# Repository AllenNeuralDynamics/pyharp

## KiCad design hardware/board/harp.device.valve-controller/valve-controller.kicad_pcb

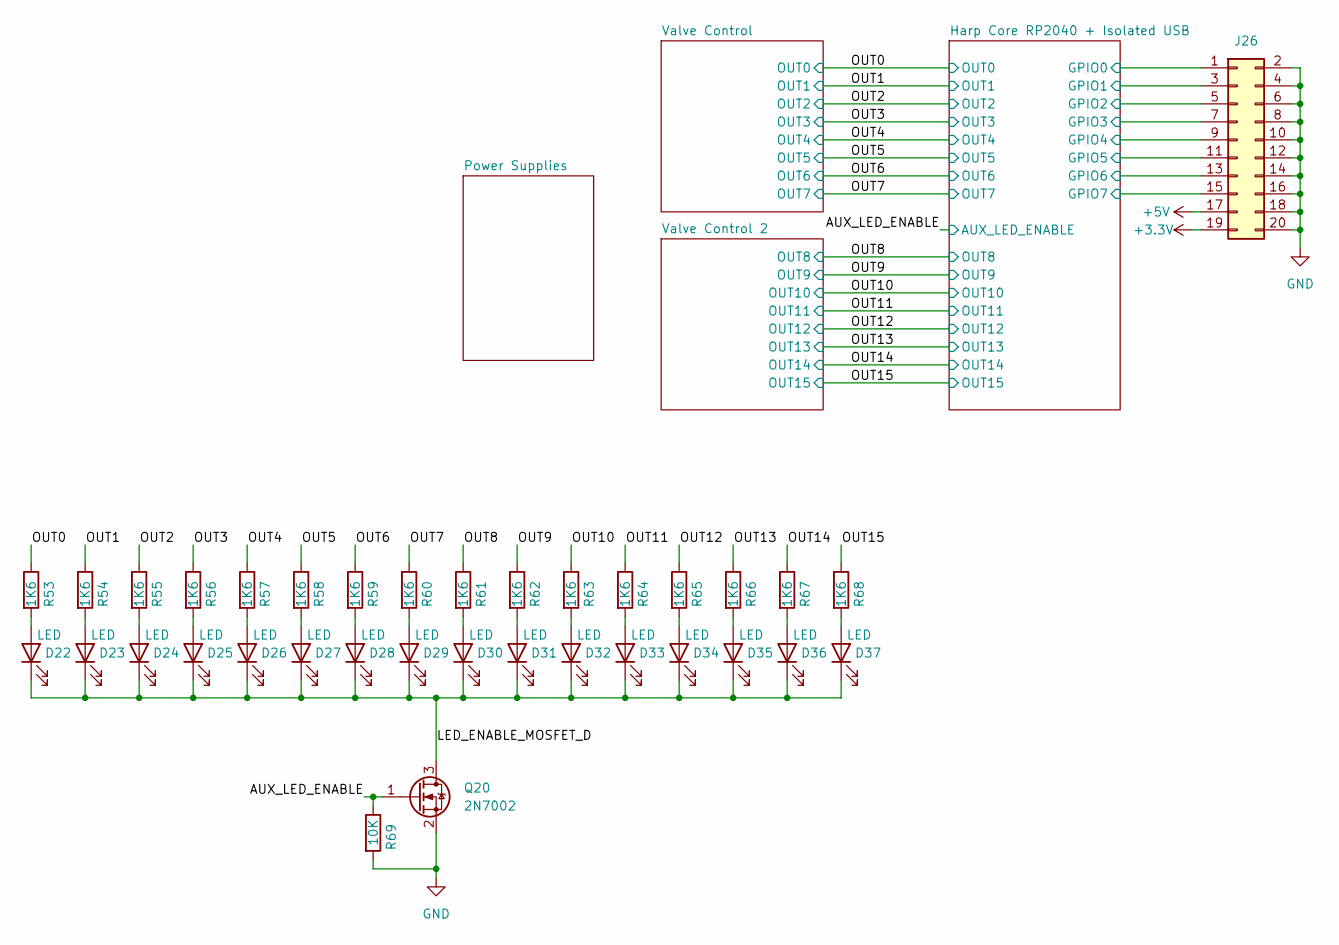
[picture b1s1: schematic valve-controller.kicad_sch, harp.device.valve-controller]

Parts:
D22, D23, D24, D25, D26, D27, D28, D29, D30, D31, D32, D33, D34, D35, D36, D37: LED; LED_0603_1608Metric_Pad1.05x0.95mm_HandSolder
J26: Conn_02x10_Odd_Even; PinHeader_2x10_P2.54mm_Vertical_SMD
Q20: 2N7002; SOT-23
R53, R54, R55, R56, R57, R58, R59, R60, R61, R62, R63, R64, R65, R66, R67, R68: 1K6; R_0402_1005Metric
R69: 10K; R_0402_1005Metric

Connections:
+3.3V: J26.19; also elsewhere on the board
+5V: J26.17; also elsewhere on the board
/AUX_LED_ENABLE: Q20.1 (G), R69.1; also elsewhere on the board
/Harp Core RP2040 + Isolated USB/GPIO0: J26.1; also elsewhere on the board
/Harp Core RP2040 + Isolated USB/GPIO1: J26.3; also elsewhere on the board
/Harp Core RP2040 + Isolated USB/GPIO2: J26.5; also elsewhere on the board
/Harp Core RP2040 + Isolated USB/GPIO3: J26.7; also elsewhere on the board
/Harp Core RP2040 + Isolated USB/GPIO4: J26.9; also elsewhere on the board
/Harp Core RP2040 + Isolated USB/GPIO5: J26.11; also elsewhere on the board
/Harp Core RP2040 + Isolated USB/GPIO6: J26.13; also elsewhere on the board
/Harp Core RP2040 + Isolated USB/GPIO7: J26.15; also elsewhere on the board
/LED_ENABLE_MOSFET_D: D22.1 (K), D23.1 (K), D24.1 (K), D25.1 (K), D26.1 (K), D27.1 (K), D28.1 (K), D29.1 (K), D30.1 (K), D31.1 (K), D32.1 (K), D33.1 (K), D34.1 (K), D35.1 (K), D36.1 (K), D37.1 (K), Q20.3 (D)
/OUT0: R53.1; also elsewhere on the board
/OUT1: R54.1; also elsewhere on the board
/OUT2: R55.1; also elsewhere on the board
/OUT3: R56.1; also elsewhere on the board
/OUT4: R57.1; also elsewhere on the board
/OUT5: R58.1; also elsewhere on the board
/OUT6: R59.1; also elsewhere on the board
/OUT7: R60.1; also elsewhere on the board
/OUT8: R61.1; also elsewhere on the board
/OUT9: R62.1; also elsewhere on the board
/OUT10: R63.1; also elsewhere on the board
/OUT11: R64.1; also elsewhere on the board
/OUT12: R65.1; also elsewhere on the board
/OUT13: R66.1; also elsewhere on the board
/OUT14: R67.1; also elsewhere on the board
/OUT15: R68.1; also elsewhere on the board
GND: J26.2, J26.4, J26.6, J26.8, J26.10, J26.12, J26.14, J26.16, J26.18, J26.20, Q20.2 (S), R69.2; also elsewhere on the board
unnamed: D22.2 (A), R53.2
unnamed: D23.2 (A), R54.2
unnamed: D24.2 (A), R55.2
unnamed: D25.2 (A), R56.2
unnamed: D26.2 (A), R57.2
unnamed: D27.2 (A), R58.2
unnamed: D28.2 (A), R59.2
unnamed: D29.2 (A), R60.2
unnamed: D30.2 (A), R61.2
unnamed: D31.2 (A), R62.2
unnamed: D32.2 (A), R63.2
unnamed: D33.2 (A), R64.2
unnamed: D34.2 (A), R65.2
unnamed: D35.2 (A), R66.2
unnamed: D36.2 (A), R67.2
unnamed: D37.2 (A), R68.2

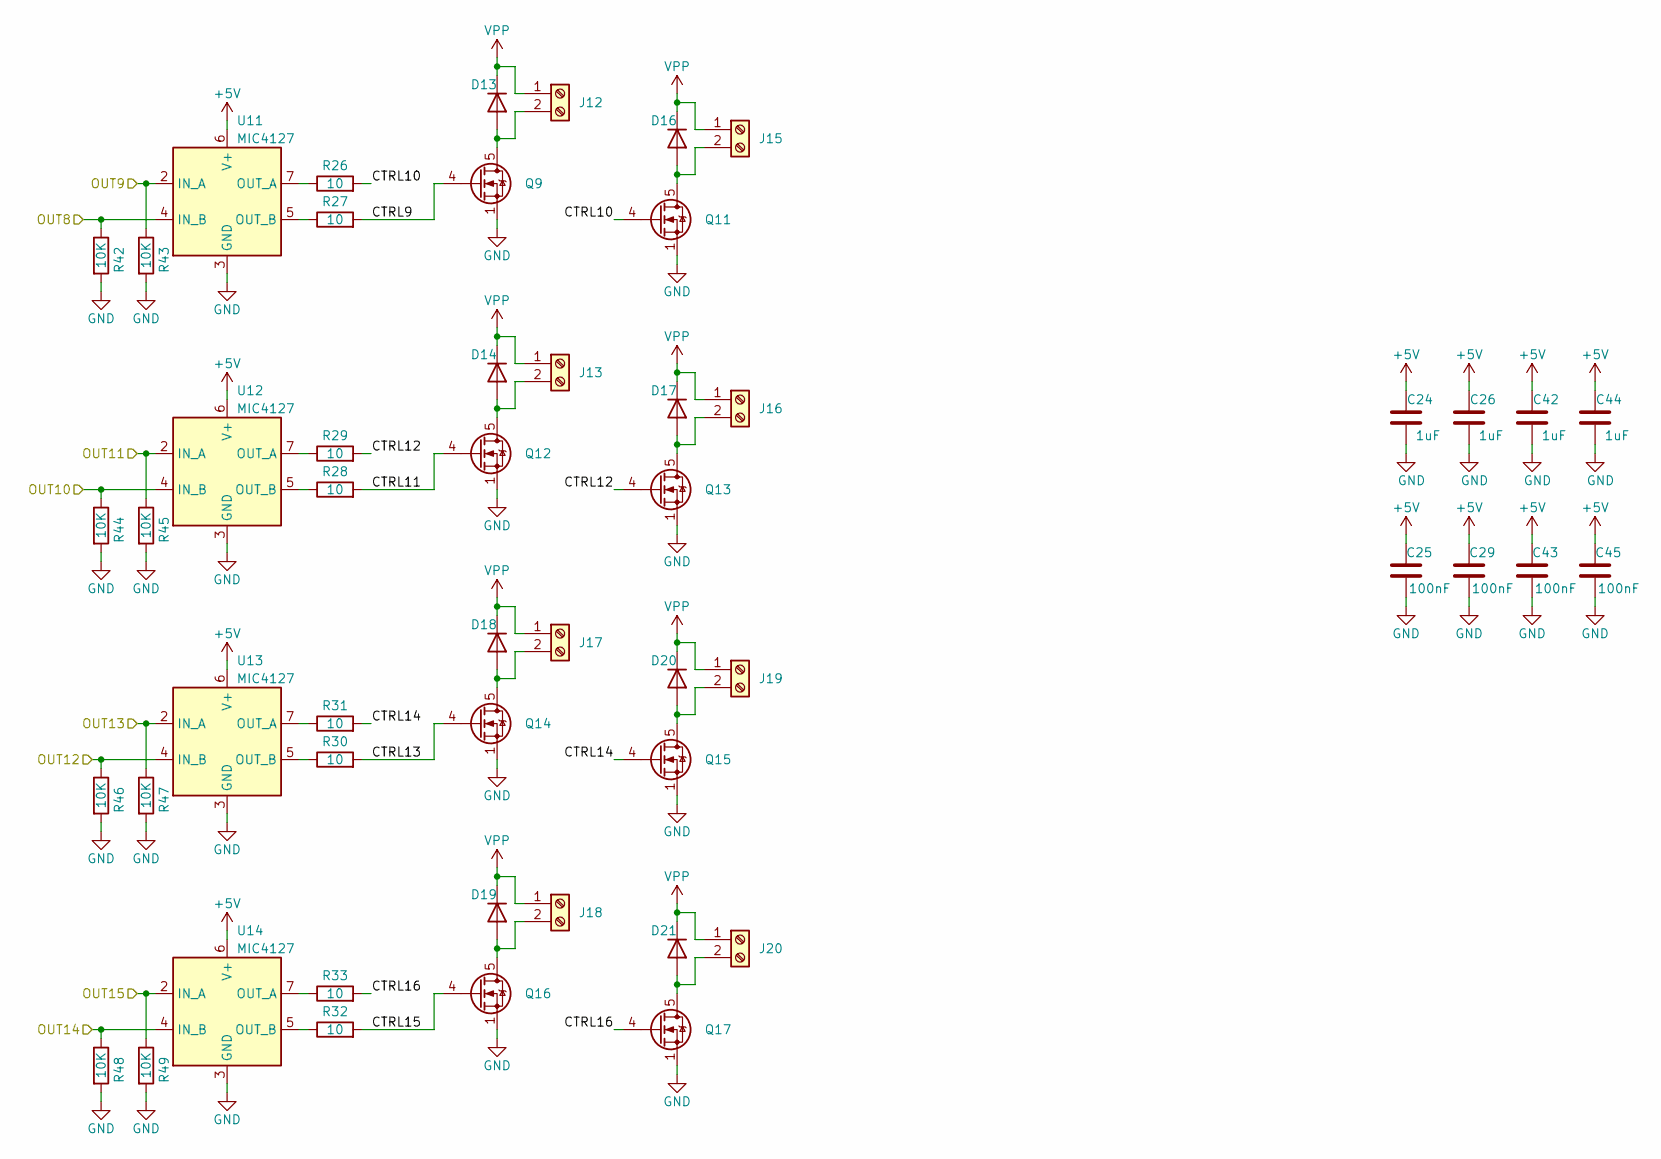
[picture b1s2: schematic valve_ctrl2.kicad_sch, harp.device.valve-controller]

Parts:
C24, C26, C42, C44: 1uF; C_0402_1005Metric; Rated Voltage 35V
C25, C29, C43, C45: 100nF; C_0402_1005Metric; Rated Voltage 50V; Tolerance 10%
D13, D14, D16, D17, D18, D19, D20, D21: 1N4007FL; D_SOD-123F
J12, J13, J15, J16, J17, J18, J19, J20: Screw_Terminal_01x02; PhoenixContact_MC_1,5_2-G-3.5_1x02_P3.50mm_Horizontal
Q9, Q11, Q12, Q13, Q14, Q15, Q16, Q17: CSD17570Q5B; TDSON-8-1
R26, R27, R28, R29, R30, R31, R32, R33: 10; R_0603_1608Metric; Tolerance 1%
R42, R43, R44, R45, R46, R47, R48, R49: 10K; R_0402_1005Metric
U11, U12, U13, U14: MIC4127; MSOP-8-1EP_3x3mm_P0.65mm_EP1.5x1.8mm

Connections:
+5V: C24.1, C25.2, C26.1, C29.2, C42.1, C43.2, C44.1, C45.2, U11.6 (V+), U12.6 (V+), U13.6 (V+), U14.6 (V+); also elsewhere on the board
/OUT8: R42.1, U11.4 (IN_B); also elsewhere on the board
/OUT9: R43.1, U11.2 (IN_A); also elsewhere on the board
/OUT10: R44.1, U12.4 (IN_B); also elsewhere on the board
/OUT11: R45.1, U12.2 (IN_A); also elsewhere on the board
/OUT12: R46.1, U13.4 (IN_B); also elsewhere on the board
/OUT13: R47.1, U13.2 (IN_A); also elsewhere on the board
/OUT14: R48.1, U14.4 (IN_B); also elsewhere on the board
/OUT15: R49.1, U14.2 (IN_A); also elsewhere on the board
/Valve Control 2/CTRL9: Q9.4 (G), R27.2
/Valve Control 2/CTRL10: Q11.4 (G), R26.2
/Valve Control 2/CTRL11: Q12.4 (G), R28.2
/Valve Control 2/CTRL12: Q13.4 (G), R29.2
/Valve Control 2/CTRL13: Q14.4 (G), R30.2
/Valve Control 2/CTRL14: Q15.4 (G), R31.2
/Valve Control 2/CTRL15: Q16.4 (G), R32.2
/Valve Control 2/CTRL16: Q17.4 (G), R33.2
GND: C24.2, C25.1, C26.2, C29.1, C42.2, C43.1, C44.2, C45.1, Q9.1 (S), Q9.2 (S), Q9.3 (S), Q11.1 (S), Q11.2 (S), Q11.3 (S), Q12.1 (S), Q12.2 (S), Q12.3 (S), Q13.1 (S), Q13.2 (S), Q13.3 (S), Q14.1 (S), Q14.2 (S), Q14.3 (S), Q15.1 (S), Q15.2 (S), Q15.3 (S), Q16.1 (S), Q16.2 (S), Q16.3 (S), Q17.1 (S), Q17.2 (S), Q17.3 (S), R42.2, R43.2, R44.2, R45.2, R46.2, R47.2, R48.2, R49.2, U11.3 (GND), U11.9 (GND), U12.3 (GND), U12.9 (GND), U13.3 (GND), U13.9 (GND), U14.3 (GND), U14.9 (GND); also elsewhere on the board
unnamed: D13.2 (A), J12.2, Q9.5 (D)
unnamed: D14.2 (A), J13.2, Q12.5 (D)
unnamed: D16.2 (A), J15.2, Q11.5 (D)
unnamed: D17.2 (A), J16.2, Q13.5 (D)
unnamed: D18.2 (A), J17.2, Q14.5 (D)
unnamed: D19.2 (A), J18.2, Q16.5 (D)
unnamed: D20.2 (A), J19.2, Q15.5 (D)
unnamed: D21.2 (A), J20.2, Q17.5 (D)
unnamed: R26.1, U11.7 (OUT_A)
unnamed: R27.1, U11.5 (OUT_B)
unnamed: R29.1, U12.7 (OUT_A)
unnamed: R28.1, U12.5 (OUT_B)
unnamed: R31.1, U13.7 (OUT_A)
unnamed: R30.1, U13.5 (OUT_B)
unnamed: R33.1, U14.7 (OUT_A)
unnamed: R32.1, U14.5 (OUT_B)
VPP: D13.1 (K), D14.1 (K), D16.1 (K), D17.1 (K), D18.1 (K), D19.1 (K), D20.1 (K), D21.1 (K), J12.1, J13.1, J15.1, J16.1, J17.1, J18.1, J19.1, J20.1; also elsewhere on the board

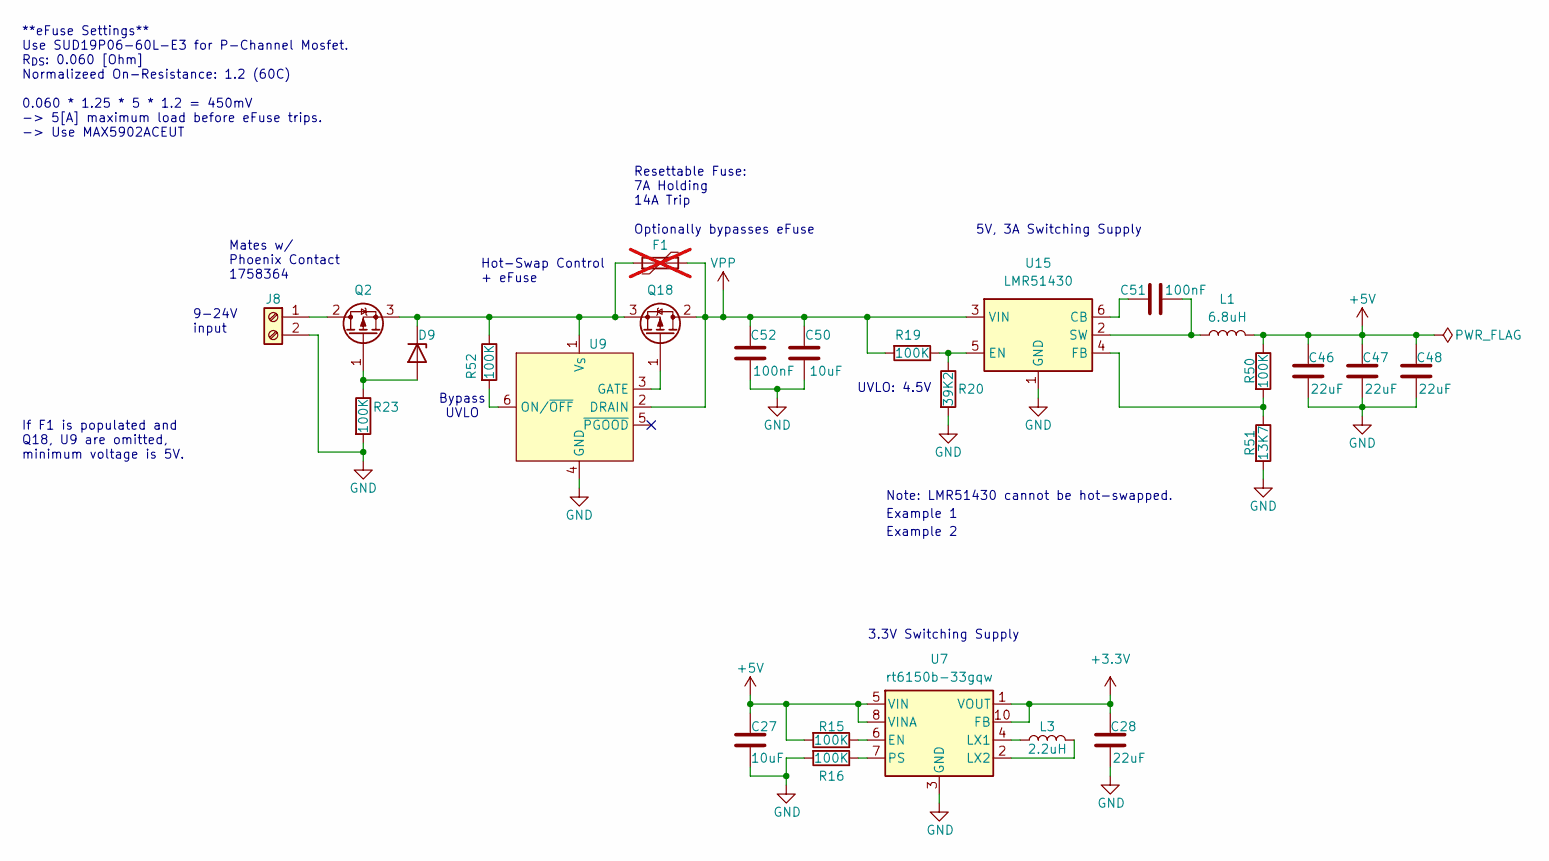
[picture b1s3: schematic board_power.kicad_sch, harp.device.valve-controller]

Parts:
C27, C50: 10uF; C_0805_2012Metric
C28, C46, C47, C48: 22uF; C_0805_2012Metric; Rated Voltage 10V
C51, C52: 100nF; C_0402_1005Metric; Rated Voltage 50V; Tolerance 10%
D9: BZV55B15; D_MiniMELF
F1: Polyfuse; Fuse_2920_7451Metric; not fitted
J8: Screw_Terminal_01x02; PhoenixContact_MSTBA_2,5_2-G-5,08_1x02_P5.08mm_Horizontal
L1: 6.8uH; L_Bourns_SRR1260
L3: 2.2uH; L_0603_1608Metric
Q2: GSFD4005; TO-252-2
Q18: SUD19P06-60L-E3; TO-252-2
R15, R16, R19, R23, R50, R52: 100K; R_0402_1005Metric; Tolerance 1%
R20: 39K2; R_0402_1005Metric; Tolerance 1%
R51: 13K7; R_0402_1005Metric; Tolerance 1%
U7: rt6150b-33gqw; WDFN-10-1EP_2.5x2.5mm_P0.5_EP1.25x2.1mm
U9: SOT-23-6
U15: LMR51430; SOT-23-6

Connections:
+3.3V: C28.2, U7.1 (VOUT), U7.10 (FB); also elsewhere on the board
+5V: C27.1, C46.2, C47.2, C48.2, L1.2, R15.2, R50.1, U7.5 (VIN), U7.8 (VINA); also elsewhere on the board
GND: C27.2, C28.1, C46.1, C47.1, C48.1, C50.2, C52.1, J8.2, R16.2, R20.2, R23.2, R51.2, U7.3 (GND), U7.9 (GND), U7.11 (GND), U9.4 (GND), U15.1 (GND); also elsewhere on the board
unnamed: D9.2 (A), Q2.1 (G), R23.1
unnamed: D9.1 (K), F1.1, Q2.3 (S), Q18.3 (S), R52.1, U9.1 (V_{S})
unnamed: J8.1, Q2.2 (D)
unnamed: Q18.1 (G), U9.3 (GATE)
unnamed: R15.1, U7.6 (EN)
unnamed: L3.1, U7.4 (LX1)
unnamed: L3.2, U7.2 (LX2)
unnamed: R16.1, U7.7 (PS)
unnamed: R52.2, U9.6 (ON/~OFF)
unnamed: C51.2, U15.6 (CB)
unnamed: R19.1, R20.1, U15.5 (EN)
unnamed: R50.2, R51.1, U15.4 (FB)
unnamed: C51.1, L1.1, U15.2 (SW)
VPP: C50.1, C52.2, F1.2, Q18.2 (D), R19.2, U9.2 (DRAIN), U15.3 (VIN); also elsewhere on the board

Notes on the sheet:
9-24V input
3.3V Switching Supply
Mates w/ Phoenix Contact 1758364
**eFuse Settings** Use SUD19P06-60L-E3 for P-Channel Mosfet. R_{DS}: 0.060 [Ohm] Normalizeed On-Resistance: 1.2 (60C) 0.060 * 1.25 * 5 * 1.2 = 450mV -> 5[A] maximum load before eFuse trips. -> Use MAX5902ACEUT
If F1 is populated and Q18, U9 are omitted, minimum voltage is 5V.
Bypass UVLO
5V, 3A Switching Supply
Note: LMR51430 cannot be hot-swapped.
Hot-Swap Control + eFuse
Example 1
Example 2
Resettable Fuse: 7A Holding 14A Trip Optionally bypasses eFuse
UVLO: 4.5V

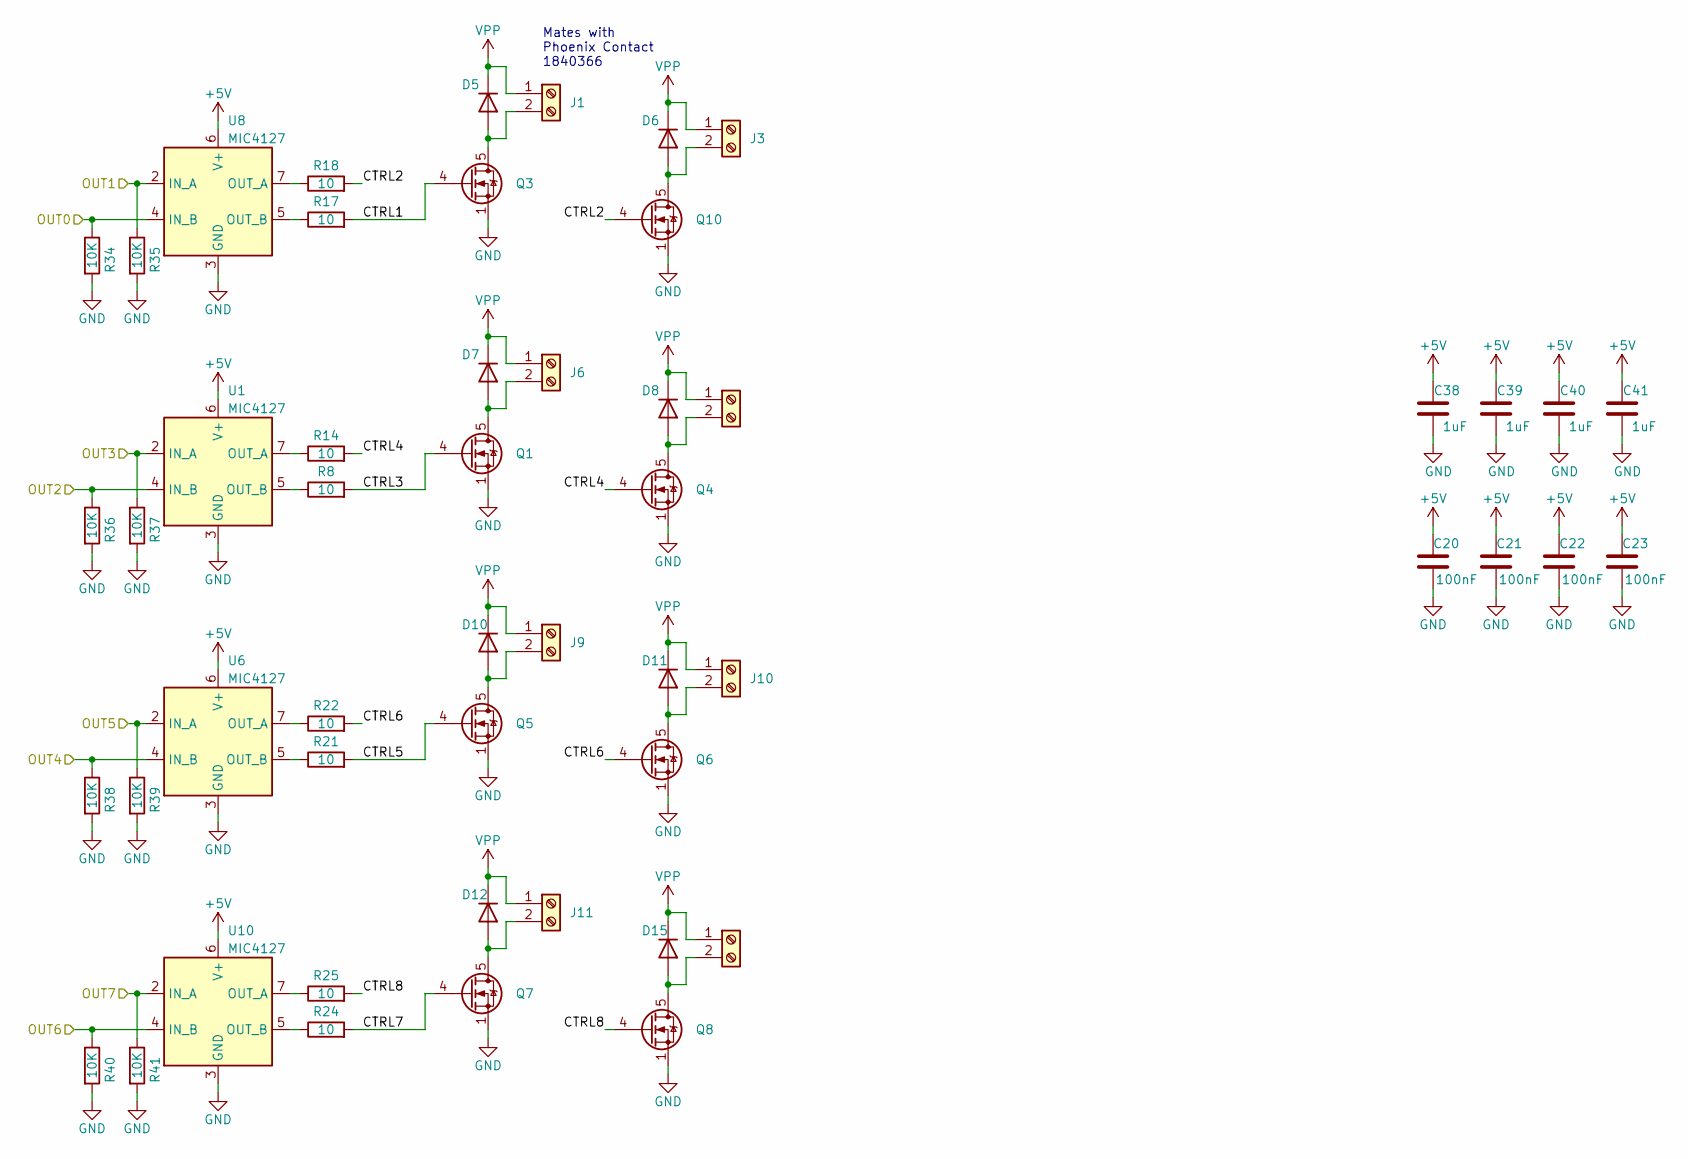
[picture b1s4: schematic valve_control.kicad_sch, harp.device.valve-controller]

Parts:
C20, C21, C22, C23: 100nF; C_0402_1005Metric; Rated Voltage 50V; Tolerance 10%
C38, C39, C40, C41: 1uF; C_0402_1005Metric; Rated Voltage 35V
D5, D6, D7, D8, D10, D11, D12, D15: 1N4007FL; D_SOD-123F
J1, J3, J6, J7, J9, J10, J11, J14: Screw_Terminal_01x02; PhoenixContact_MC_1,5_2-G-3.5_1x02_P3.50mm_Horizontal
Q1, Q3, Q4, Q5, Q6, Q7, Q8, Q10: CSD17570Q5B; TDSON-8-1
R8, R14, R17, R18, R21, R22, R24, R25: 10; R_0603_1608Metric; Tolerance 1%
R34, R35, R36, R37, R38, R39, R40, R41: 10K; R_0402_1005Metric
U1, U6, U8, U10: MIC4127; MSOP-8-1EP_3x3mm_P0.65mm_EP1.5x1.8mm

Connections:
+5V: C20.2, C21.2, C22.2, C23.2, C38.1, C39.1, C40.1, C41.1, U1.6 (V+), U6.6 (V+), U8.6 (V+), U10.6 (V+); also elsewhere on the board
/OUT0: R34.1, U8.4 (IN_B); also elsewhere on the board
/OUT1: R35.1, U8.2 (IN_A); also elsewhere on the board
/OUT2: R36.1, U1.4 (IN_B); also elsewhere on the board
/OUT3: R37.1, U1.2 (IN_A); also elsewhere on the board
/OUT4: R38.1, U6.4 (IN_B); also elsewhere on the board
/OUT5: R39.1, U6.2 (IN_A); also elsewhere on the board
/OUT6: R40.1, U10.4 (IN_B); also elsewhere on the board
/OUT7: R41.1, U10.2 (IN_A); also elsewhere on the board
/Valve Control/CTRL1: Q3.4 (G), R17.2
/Valve Control/CTRL2: Q10.4 (G), R18.2
/Valve Control/CTRL3: Q1.4 (G), R8.2
/Valve Control/CTRL4: Q4.4 (G), R14.2
/Valve Control/CTRL5: Q5.4 (G), R21.2
/Valve Control/CTRL6: Q6.4 (G), R22.2
/Valve Control/CTRL7: Q7.4 (G), R24.2
/Valve Control/CTRL8: Q8.4 (G), R25.2
GND: C20.1, C21.1, C22.1, C23.1, C38.2, C39.2, C40.2, C41.2, Q1.1 (S), Q1.2 (S), Q1.3 (S), Q3.1 (S), Q3.2 (S), Q3.3 (S), Q4.1 (S), Q4.2 (S), Q4.3 (S), Q5.1 (S), Q5.2 (S), Q5.3 (S), Q6.1 (S), Q6.2 (S), Q6.3 (S), Q7.1 (S), Q7.2 (S), Q7.3 (S), Q8.1 (S), Q8.2 (S), Q8.3 (S), Q10.1 (S), Q10.2 (S), Q10.3 (S), R34.2, R35.2, R36.2, R37.2, R38.2, R39.2, R40.2, R41.2, U1.3 (GND), U1.9 (GND), U6.3 (GND), U6.9 (GND), U8.3 (GND), U8.9 (GND), U10.3 (GND), U10.9 (GND); also elsewhere on the board
unnamed: D5.2 (A), J1.2, Q3.5 (D)
unnamed: D6.2 (A), J3.2, Q10.5 (D)
unnamed: D7.2 (A), J6.2, Q1.5 (D)
unnamed: D8.2 (A), J7.2, Q4.5 (D)
unnamed: D10.2 (A), J9.2, Q5.5 (D)
unnamed: D11.2 (A), J10.2, Q6.5 (D)
unnamed: D12.2 (A), J11.2, Q7.5 (D)
unnamed: D15.2 (A), J14.2, Q8.5 (D)
unnamed: R14.1, U1.7 (OUT_A)
unnamed: R8.1, U1.5 (OUT_B)
unnamed: R22.1, U6.7 (OUT_A)
unnamed: R21.1, U6.5 (OUT_B)
unnamed: R18.1, U8.7 (OUT_A)
unnamed: R17.1, U8.5 (OUT_B)
unnamed: R25.1, U10.7 (OUT_A)
unnamed: R24.1, U10.5 (OUT_B)
VPP: D5.1 (K), D6.1 (K), D7.1 (K), D8.1 (K), D10.1 (K), D11.1 (K), D12.1 (K), D15.1 (K), J1.1, J3.1, J6.1, J7.1, J9.1, J10.1, J11.1, J14.1; also elsewhere on the board

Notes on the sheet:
Mates with Phoenix Contact 1840366

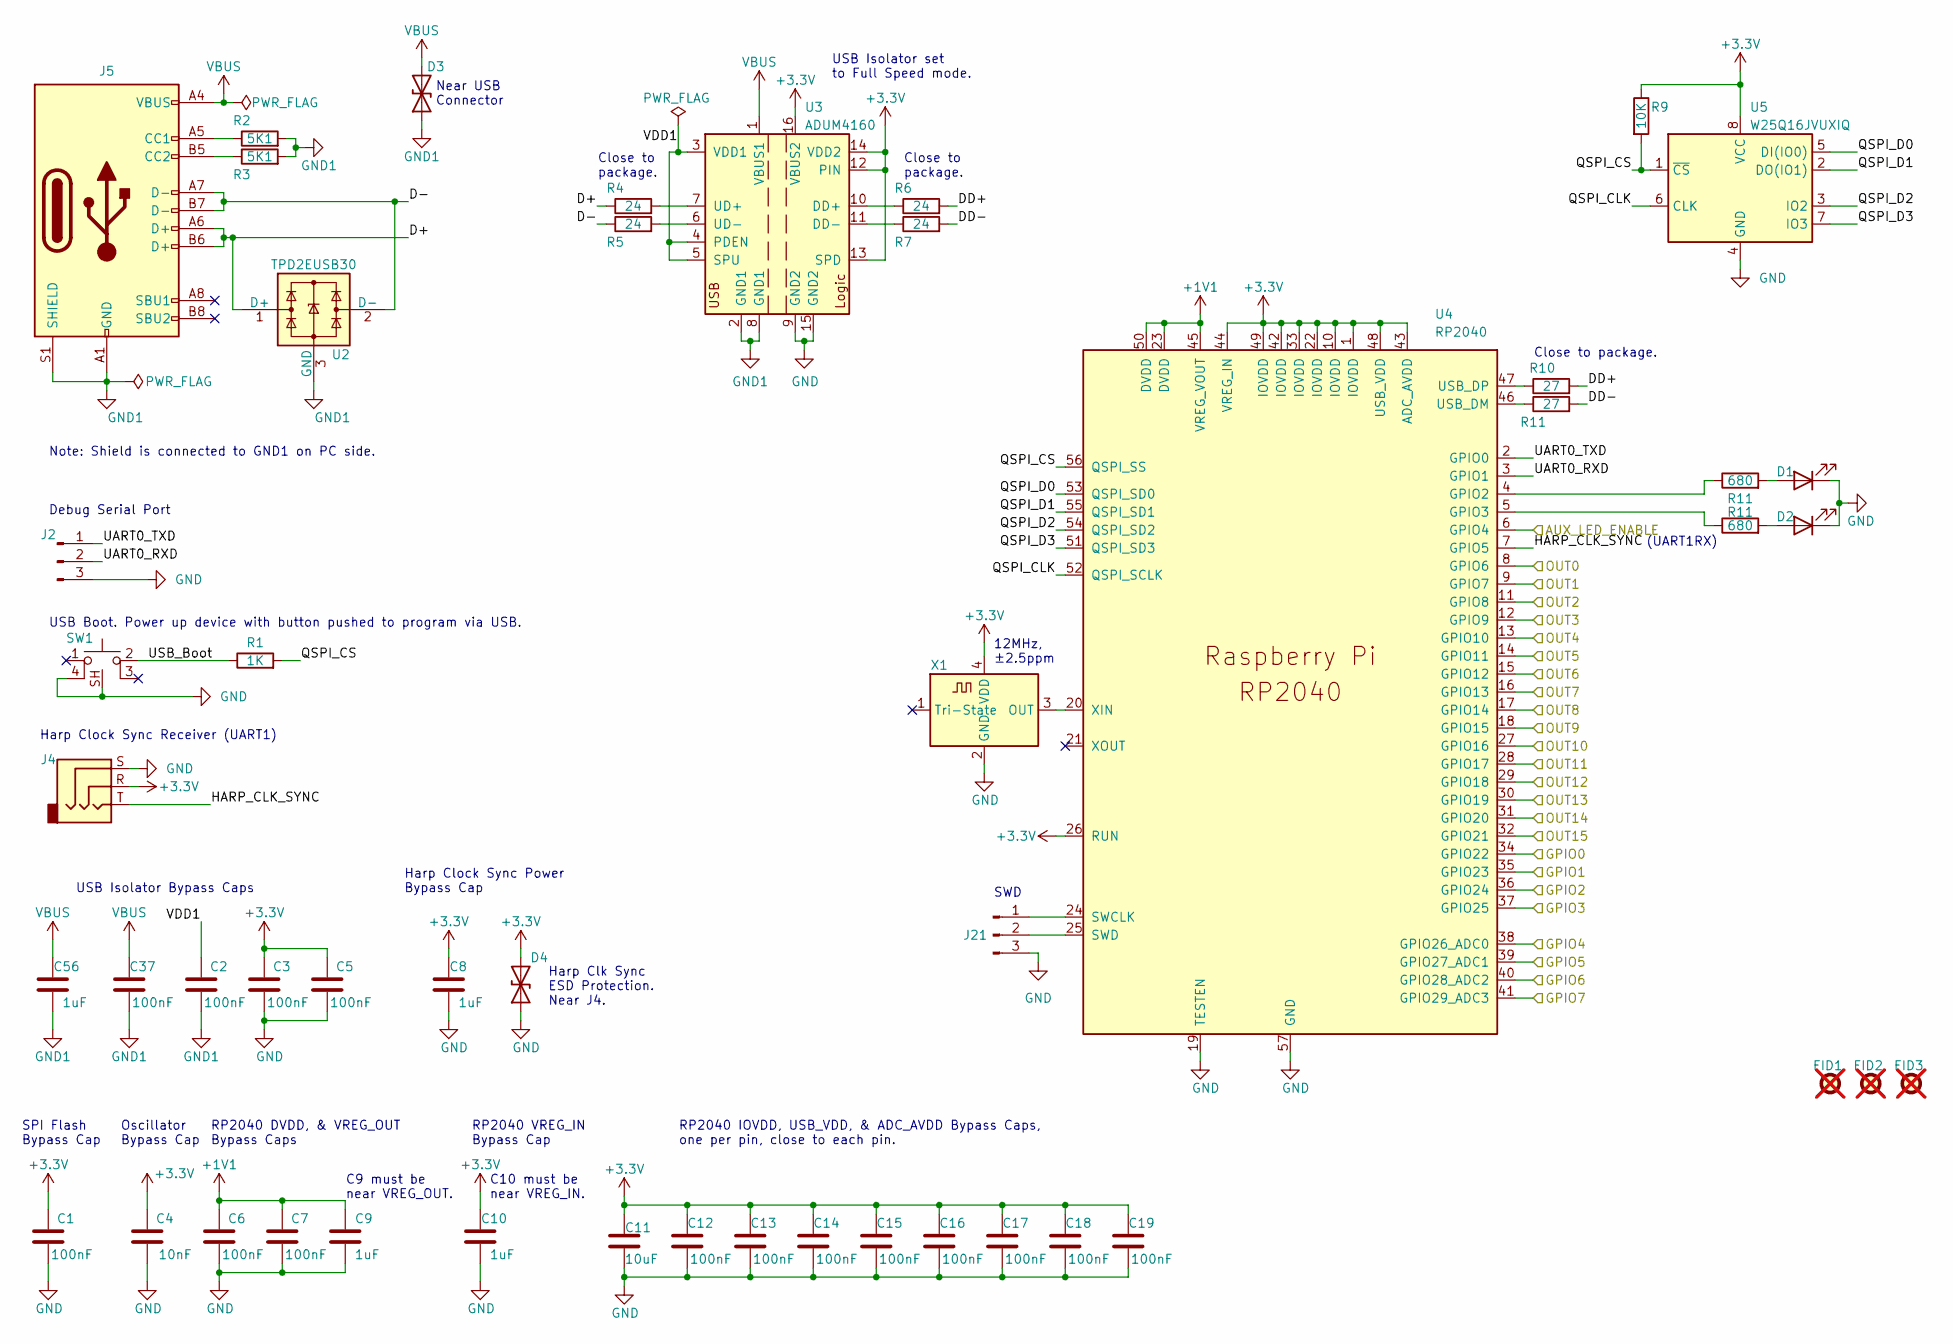
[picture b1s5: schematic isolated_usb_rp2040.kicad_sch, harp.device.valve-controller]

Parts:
C1, C2, C3, C5, C6, C7, C12, C13, C14, C15, C16, C17, C18, C19, C37: 100nF; C_0402_1005Metric; Rated Voltage 50V; Tolerance 10%
C4: 10nF; C_0402_1005Metric; Rated Voltage 25V; Tolerance 10%
C8, C9, C10, C56: 1uF; C_0402_1005Metric; Rated Voltage 35V
C11: 10uF; C_0805_2012Metric
D1, D2: LED; LED_0603_1608Metric_Pad1.05x0.95mm_HandSolder
D3, D4: D_TVS; D_0402_1005Metric
FID1, FID2, FID3: Fiducial; Fiducial_0.5mm_Mask1mm; not fitted
J2, J21: Conn_01x03_Male; PinHeader_1x03_P2.54mm_Vertical
J4: AudioJack3; Jack_3.5mm_CUI_SJ-3524-SMT_Horizontal
J5: USB_C_Receptacle_USB2.0; USB_C_Receptacle_JAE_DX07S016JA1R1500
R1: 1K; R_0402_1005Metric; Tolerance 1%
R2, R3: 5K1; R_0402_1005Metric; Tolerance 1%
R4, R5, R6, R7: 24; R_0402_1005Metric; Tolerance 1%
R9: 10K; R_0402_1005Metric
R10, R11: 27; R_0402_1005Metric; Tolerance 1%
SW1: SW_Push_1P1T-SH_NO_Vertical_Wuerth_WS-TASV
U2: TPD2EUSB30; Texas_DRT-3
U3: ADUM4160; SOIC-16W_7.5x10.3mm_P1.27mm
U4: RP2040; RP2040-QFN-56
U5: W25Q16JVUXIQ; Winbond-8USON-2x3mm
X1: ECS-TXO-2016; Crystal_SMD_2016-4Pin_2.0x1.6mm; Tolerance ±2.5ppm

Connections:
+1V1: C6.2, C7.2, C9.1, U4.23 (DVDD), U4.45 (VREG_VOUT), U4.50 (DVDD)
+3.3V: C1.2, C3.2, C4.2, C5.2, C8.1, C10.1, C11.1, C12.2, C13.2, C14.2, C15.2, C16.2, C17.2, C18.2, C19.2, D4.2 (A2), J4.R, R9.1, U3.12 (PIN), U3.13 (SPD), U3.14 (VDD2), U3.16 (VBUS2), U4.1 (IOVDD), U4.10 (IOVDD), U4.22 (IOVDD), U4.26 (RUN), U4.33 (IOVDD), U4.42 (IOVDD), U4.43 (ADC_AVDD), U4.44 (VREG_IN), U4.48 (USB_VDD), U4.49 (IOVDD), U5.8 (VCC), X1.4 (VDD); also elsewhere on the board
/AUX_LED_ENABLE: U4.6 (GPIO4); also elsewhere on the board
/Harp Core RP2040 + Isolated USB/D+: J5.A6 (D+), J5.B6 (D+), R4.1, U2.1 (D+)
/Harp Core RP2040 + Isolated USB/D-: J5.A7 (D-), J5.B7 (D-), R5.1, U2.2 (D-)
/Harp Core RP2040 + Isolated USB/DD+: R6.2, R10.2
/Harp Core RP2040 + Isolated USB/GPIO0: U4.34 (GPIO22); also elsewhere on the board
/Harp Core RP2040 + Isolated USB/GPIO1: U4.35 (GPIO23); also elsewhere on the board
/Harp Core RP2040 + Isolated USB/GPIO2: U4.36 (GPIO24); also elsewhere on the board
/Harp Core RP2040 + Isolated USB/GPIO3: U4.37 (GPIO25); also elsewhere on the board
/Harp Core RP2040 + Isolated USB/GPIO4: U4.38 (GPIO26_ADC0); also elsewhere on the board
/Harp Core RP2040 + Isolated USB/GPIO5: U4.39 (GPIO27_ADC1); also elsewhere on the board
/Harp Core RP2040 + Isolated USB/GPIO6: U4.40 (GPIO28_ADC2); also elsewhere on the board
/Harp Core RP2040 + Isolated USB/GPIO7: U4.41 (GPIO29_ADC3); also elsewhere on the board
/Harp Core RP2040 + Isolated USB/HARP_CLK_SYNC: J4.T, U4.7 (GPIO5)
/Harp Core RP2040 + Isolated USB/QSPI_CLK: U4.52 (QSPI_SCLK), U5.6 (CLK)
/Harp Core RP2040 + Isolated USB/QSPI_CS: R1.2, R9.2, U4.56 (QSPI_SS), U5.1 (~CS)
/Harp Core RP2040 + Isolated USB/QSPI_D0: U4.53 (QSPI_SD0), U5.5 (DI(IO0))
/Harp Core RP2040 + Isolated USB/QSPI_D1: U4.55 (QSPI_SD1), U5.2 (DO(IO1))
/Harp Core RP2040 + Isolated USB/QSPI_D2: U4.54 (QSPI_SD2), U5.3 (IO2)
/Harp Core RP2040 + Isolated USB/QSPI_D3: U4.51 (QSPI_SD3), U5.7 (IO3)
/Harp Core RP2040 + Isolated USB/UART0_RXD: J2.2, U4.3 (GPIO1)
/Harp Core RP2040 + Isolated USB/UART0_TXD: J2.1, U4.2 (GPIO0)
/Harp Core RP2040 + Isolated USB/USB_Boot: R1.1, SW1.2
/Harp Core RP2040 + Isolated USB/VDD1: C2.2, U3.3 (VDD1), U3.4 (PDEN), U3.5 (SPU)
/OUT0: U4.8 (GPIO6); also elsewhere on the board
/OUT1: U4.9 (GPIO7); also elsewhere on the board
/OUT2: U4.11 (GPIO8); also elsewhere on the board
/OUT3: U4.12 (GPIO9); also elsewhere on the board
/OUT4: U4.13 (GPIO10); also elsewhere on the board
/OUT5: U4.14 (GPIO11); also elsewhere on the board
/OUT6: U4.15 (GPIO12); also elsewhere on the board
/OUT7: U4.16 (GPIO13); also elsewhere on the board
/OUT8: U4.17 (GPIO14); also elsewhere on the board
/OUT9: U4.18 (GPIO15); also elsewhere on the board
/OUT10: U4.27 (GPIO16); also elsewhere on the board
/OUT11: U4.28 (GPIO17); also elsewhere on the board
/OUT12: U4.29 (GPIO18); also elsewhere on the board
/OUT13: U4.30 (GPIO19); also elsewhere on the board
/OUT14: U4.31 (GPIO20); also elsewhere on the board
/OUT15: U4.32 (GPIO21); also elsewhere on the board
GND: C1.1, C3.1, C4.1, C5.1, C6.1, C7.1, C8.2, C9.2, C10.2, C11.2, C12.1, C13.1, C14.1, C15.1, C16.1, C17.1, C18.1, C19.1, D1.1 (K), D2.1 (K), D4.1 (A1), J2.3, J4.S, J21.3, SW1.4, SW1.SH, U3.9 (GND2), U3.15 (GND2), U4.19 (TESTEN), U4.57 (GND), U5.4 (GND), X1.2 (GND); also elsewhere on the board
GND1: C2.1, C37.1, C56.2, D3.1 (A1), J5.A1 (GND), J5.A12 (GND), J5.B1 (GND), J5.B12 (GND), J5.S1 (SHIELD), R2.2, R3.2, U2.3 (GND), U3.2 (GND1), U3.8 (GND1)
unnamed: J5.A5 (CC1), R2.1
unnamed: J5.B5 (CC2), R3.1
unnamed: J21.1, U4.24 (SWCLK)
unnamed: J21.2, U4.25 (SWD)
unnamed: R6.1, U3.10 (DD+)
unnamed: R7.1, U3.11 (DD-)
unnamed: R4.2, U3.7 (UD+)
unnamed: R5.2, U3.6 (UD-)
unnamed: R10.1, U4.47 (USB_DP)
unnamed: U4.20 (XIN), X1.3 (OUT)
VBUS: C37.2, C56.1, D3.2 (A2), J5.A4 (VBUS), J5.A9 (VBUS), J5.B4 (VBUS), J5.B9 (VBUS), U3.1 (VBUS1)

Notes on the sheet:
Close to package.
SWD
Near USB Connector
Close to package.
(UART1RX)
Harp Clk Sync ESD Protection. Near J4.
RP2040 VREG_IN Bypass Cap
Oscillator Bypass Cap
Harp Clock Sync Power Bypass Cap
C10 must be near VREG_IN.
RP2040 DVDD, & VREG_OUT Bypass Caps
Debug Serial Port
USB Boot. Power up device with button pushed to program via USB.
C9 must be near VREG_OUT.
Harp Clock Sync Receiver (UART1)
12MHz, ±2.5ppm
Note: Shield is connected to GND1 on PC side.
RP2040 IOVDD, USB_VDD, & ADC_AVDD Bypass Caps, one per pin, close to each pin.
USB Isolator Bypass Caps
SPI Flash Bypass Cap
USB Isolator set to Full Speed mode.

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
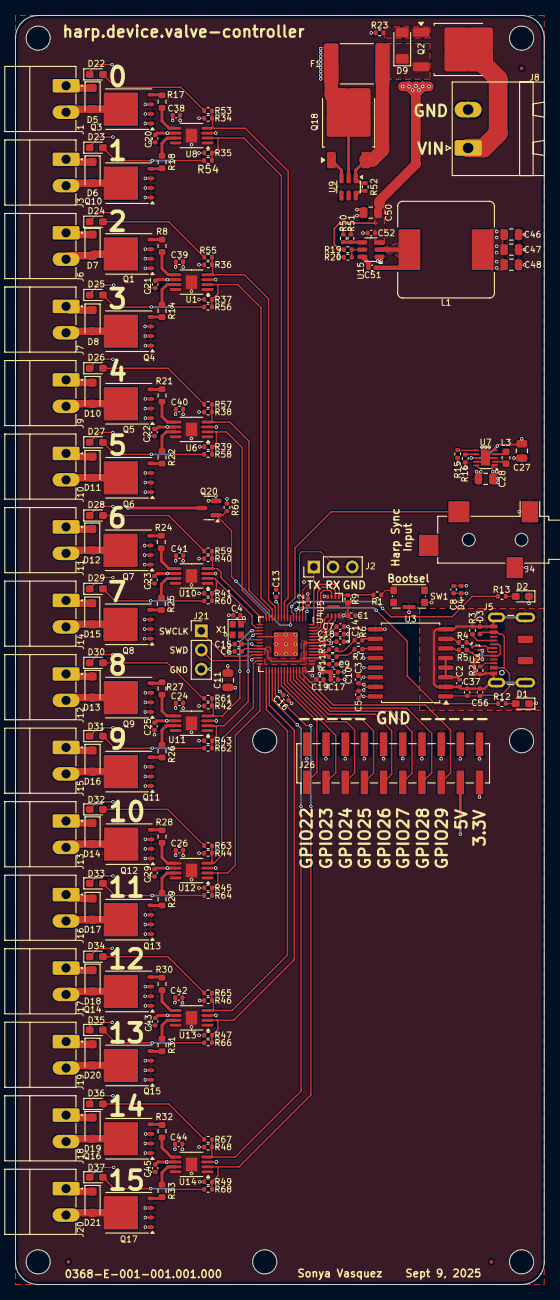
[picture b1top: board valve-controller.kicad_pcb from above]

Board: 4 copper layers, 70.0 x 168.0 mm, 216 parts (1 on the bottom side), 140 nets.

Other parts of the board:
R12, R13: 680; R_0402_1005Metric
REF1: OSHW-Logo2_7.3x6mm_SilkScreen

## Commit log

2022-04-23 scaffolding thread interface
2024-05-17 Added ReadS32 and refactored WriteS32 to handle array inputs
2024-09-09 add u8 arrays
2024-10-30 Add threaded serial port
2025-02-12 clean up formatting changes
2025-02-12 add event_count method and update test
2025-02-12 remove unused import
2025-02-12 undo formatting change
2025-02-12 remove python-versions pin
2025-02-13 add heartbeat en/disable fns
2025-02-13 add future import for list annotations
2025-02-13 fix future import
2025-02-21 update wait-for-events example
2025-02-21 remove extraneous call
2025-02-21 undo get info example change
2025-02-21 undo unused test
2025-06-06 name harpserial threads; make both daemon threads
2025-06-09 add debug log message
2025-09-09 add soft start ic; add status LEDs per output
